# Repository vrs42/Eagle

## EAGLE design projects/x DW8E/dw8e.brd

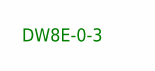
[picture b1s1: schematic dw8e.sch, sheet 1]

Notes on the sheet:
DW8E-0-3

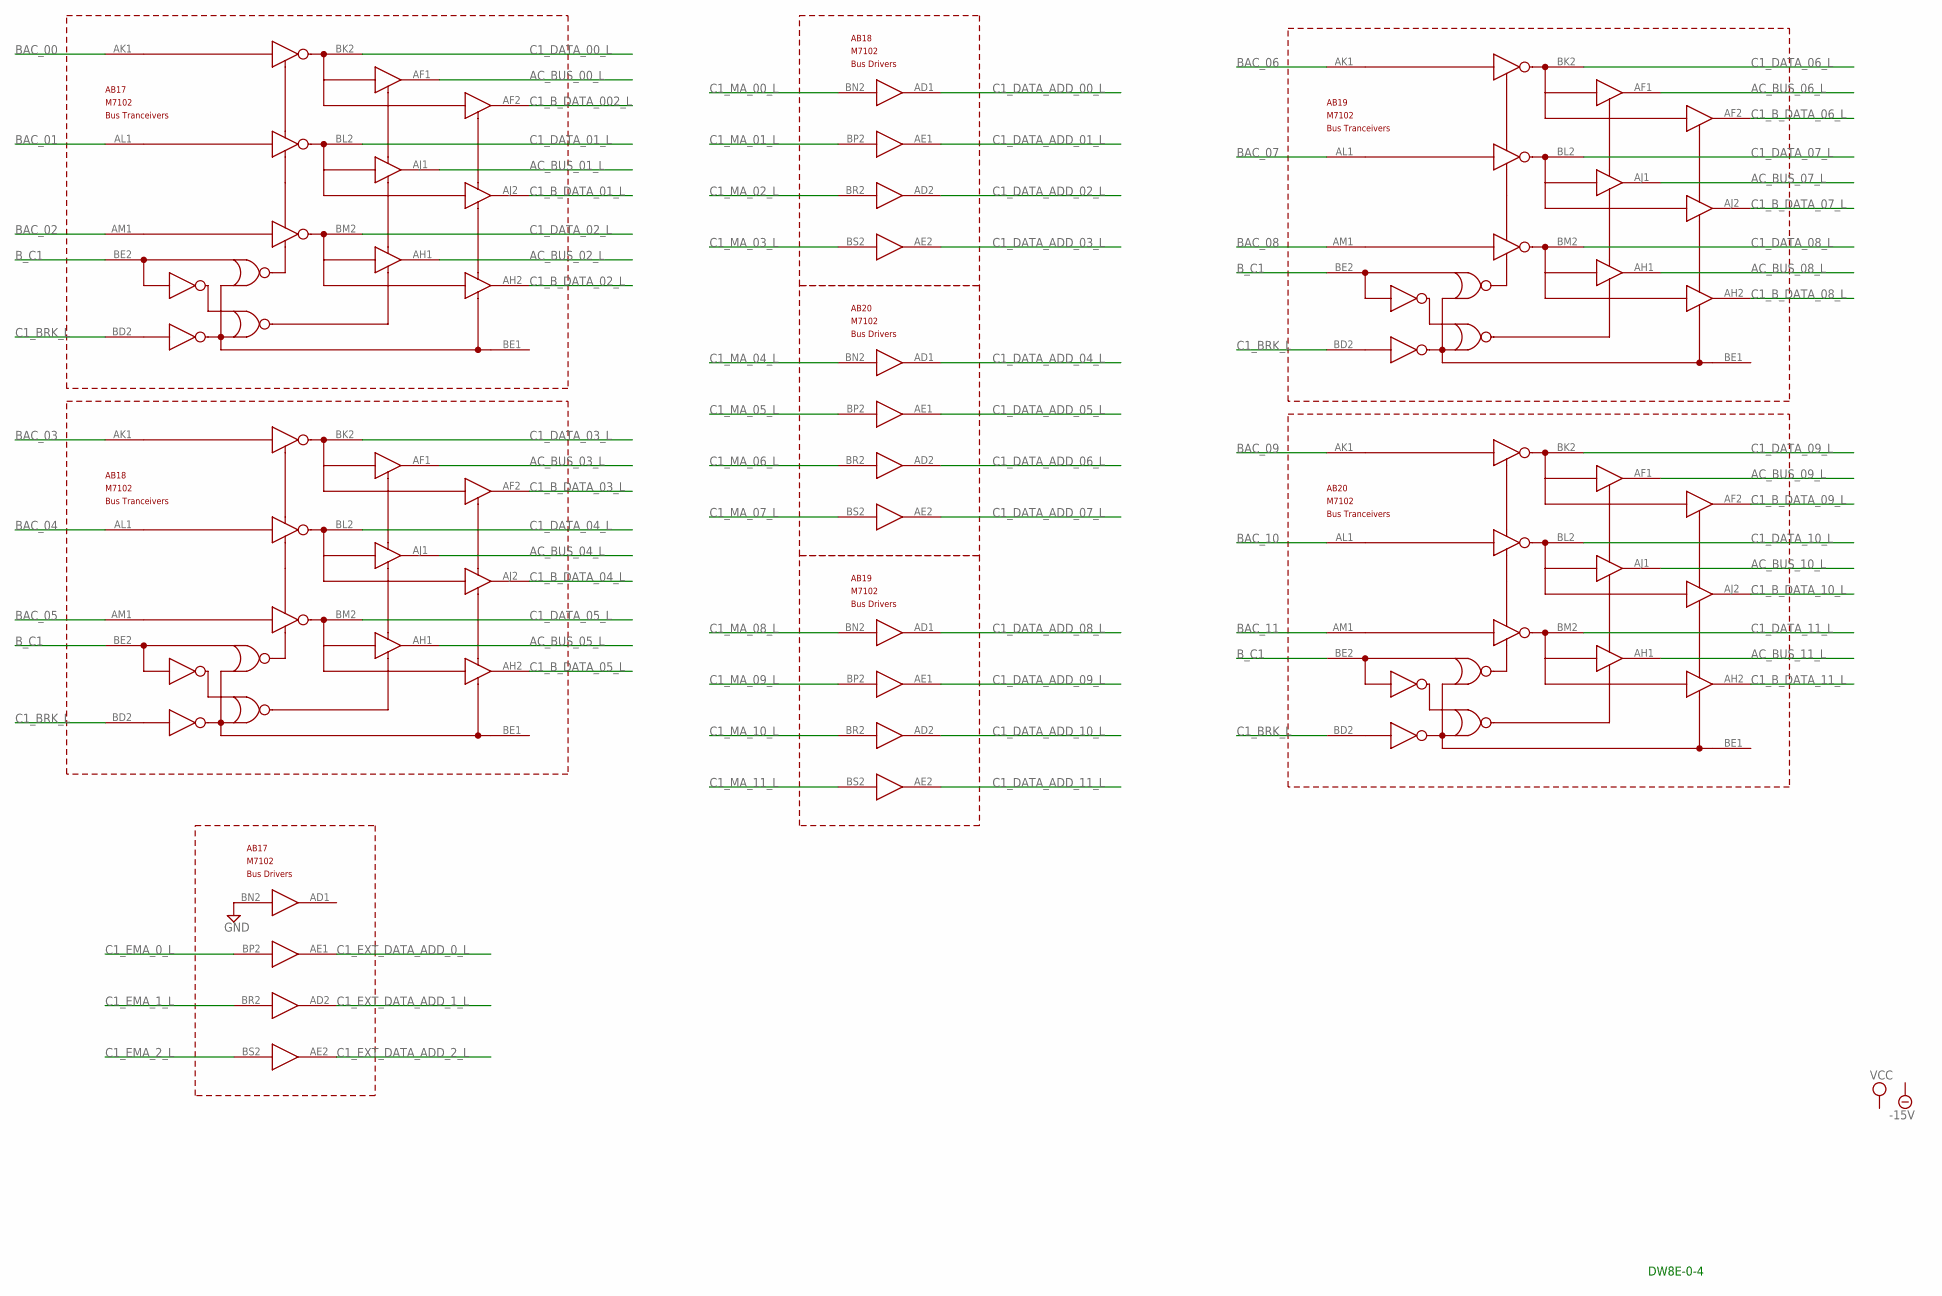
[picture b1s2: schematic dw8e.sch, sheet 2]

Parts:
AB17, AB18, AB19, AB20: M7102; H807-2

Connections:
-15V: AB17.AB2 (-15V), AB17.BB2 (-15V), AB18.AB2 (-15V), AB18.BB2 (-15V), AB19.AB2 (-15V), AB19.BB2 (-15V), AB20.AB2 (-15V), AB20.BB2 (-15V); also elsewhere on the board
AC_BUS_00_L: AB17.AF1
AC_BUS_01_L: AB17.AJ1
AC_BUS_02_L: AB17.AH1
AC_BUS_03_L: AB18.AF1
AC_BUS_04_L: AB18.AJ1
AC_BUS_05_L: AB18.AH1
AC_BUS_06_L: AB19.AF1
AC_BUS_07_L: AB19.AJ1
AC_BUS_08_L: AB19.AH1
AC_BUS_09_L: AB20.AF1
AC_BUS_10_L: AB20.AJ1
AC_BUS_11_L: AB20.AH1
BAC_00: AB17.AK1; also elsewhere on the board
BAC_01: AB17.AL1; also elsewhere on the board
BAC_02: AB17.AM1; also elsewhere on the board
BAC_03: AB18.AK1; also elsewhere on the board
BAC_04: AB18.AL1; also elsewhere on the board
BAC_05: AB18.AM1; also elsewhere on the board
BAC_06: AB19.AK1; also elsewhere on the board
BAC_07: AB19.AL1; also elsewhere on the board
BAC_08: AB19.AM1; also elsewhere on the board
BAC_09: AB20.AK1; also elsewhere on the board
BAC_10: AB20.AL1; also elsewhere on the board
BAC_11: AB20.AM1; also elsewhere on the board
B_C1: AB17.BE2, AB18.BE2, AB19.BE2, AB20.BE2
C1_BRK_L: AB17.BD2, AB18.BD2, AB19.BD2, AB20.BD2; also elsewhere on the board
C1_B_DATA_01_L: AB17.AJ2
C1_B_DATA_002_L: AB17.AF2
C1_B_DATA_02_L: AB17.AH2
C1_B_DATA_03_L: AB18.AF2
C1_B_DATA_04_L: AB18.AJ2
C1_B_DATA_05_L: AB18.AH2
C1_B_DATA_06_L: AB19.AF2
C1_B_DATA_07_L: AB19.AJ2
C1_B_DATA_08_L: AB19.AH2
C1_B_DATA_09_L: AB20.AF2
C1_B_DATA_10_L: AB20.AJ2
C1_B_DATA_11_L: AB20.AH2
C1_DATA_00_L: AB17.BK2
C1_DATA_01_L: AB17.BL2
C1_DATA_02_L: AB17.BM2
C1_DATA_03_L: AB18.BK2
C1_DATA_04_L: AB18.BL2
C1_DATA_05_L: AB18.BM2
C1_DATA_06_L: AB19.BK2
C1_DATA_07_L: AB19.BL2
C1_DATA_08_L: AB19.BM2
C1_DATA_09_L: AB20.BK2
C1_DATA_10_L: AB20.BL2
C1_DATA_11_L: AB20.BM2
C1_DATA_ADD_00_L: AB18.AD1; also elsewhere on the board
C1_DATA_ADD_01_L: AB18.AE1; also elsewhere on the board
C1_DATA_ADD_02_L: AB18.AD2; also elsewhere on the board
C1_DATA_ADD_03_L: AB18.AE2; also elsewhere on the board
C1_DATA_ADD_04_L: AB20.AD1; also elsewhere on the board
C1_DATA_ADD_05_L: AB20.AE1; also elsewhere on the board
C1_DATA_ADD_06_L: AB20.AD2; also elsewhere on the board
C1_DATA_ADD_07_L: AB20.AE2; also elsewhere on the board
C1_DATA_ADD_08_L: AB19.AD1; also elsewhere on the board
C1_DATA_ADD_09_L: AB19.AE1; also elsewhere on the board
C1_DATA_ADD_10_L: AB19.AD2; also elsewhere on the board
C1_DATA_ADD_11_L: AB19.AE2; also elsewhere on the board
C1_EMA_0_L: AB17.BP2
C1_EMA_1_L: AB17.BR2
C1_EMA_2_L: AB17.BS2
C1_EXT_DATA_ADD_0_L: AB17.AE1; also elsewhere on the board
C1_EXT_DATA_ADD_1_L: AB17.AD2; also elsewhere on the board
C1_EXT_DATA_ADD_2_L: AB17.AE2; also elsewhere on the board
C1_MA_00_L: AB18.BN2
C1_MA_01_L: AB18.BP2
C1_MA_02_L: AB18.BR2
C1_MA_03_L: AB18.BS2
C1_MA_04_L: AB20.BN2
C1_MA_05_L: AB20.BP2
C1_MA_06_L: AB20.BR2
C1_MA_07_L: AB20.BS2
C1_MA_08_L: AB19.BN2
C1_MA_09_L: AB19.BP2
C1_MA_10_L: AB19.BR2
C1_MA_11_L: AB19.BS2
GND: AB17.AC2 (GND), AB17.AT1 (GND), AB17.BC2 (GND), AB17.BN2, AB17.BT1 (GND), AB18.AC2 (GND), AB18.AT1 (GND), AB18.BC2 (GND), AB18.BT1 (GND), AB19.AC2 (GND), AB19.AT1 (GND), AB19.BC2 (GND), AB19.BT1 (GND), AB20.AC2 (GND), AB20.AT1 (GND), AB20.BC2 (GND), AB20.BT1 (GND); also elsewhere on the board
VCC: AB17.AA2 (VCC), AB17.BA2 (VCC), AB18.AA2 (VCC), AB18.BA2 (VCC), AB19.AA2 (VCC), AB19.BA2 (VCC), AB20.AA2 (VCC), AB20.BA2 (VCC); also elsewhere on the board

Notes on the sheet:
DW8E-0-4

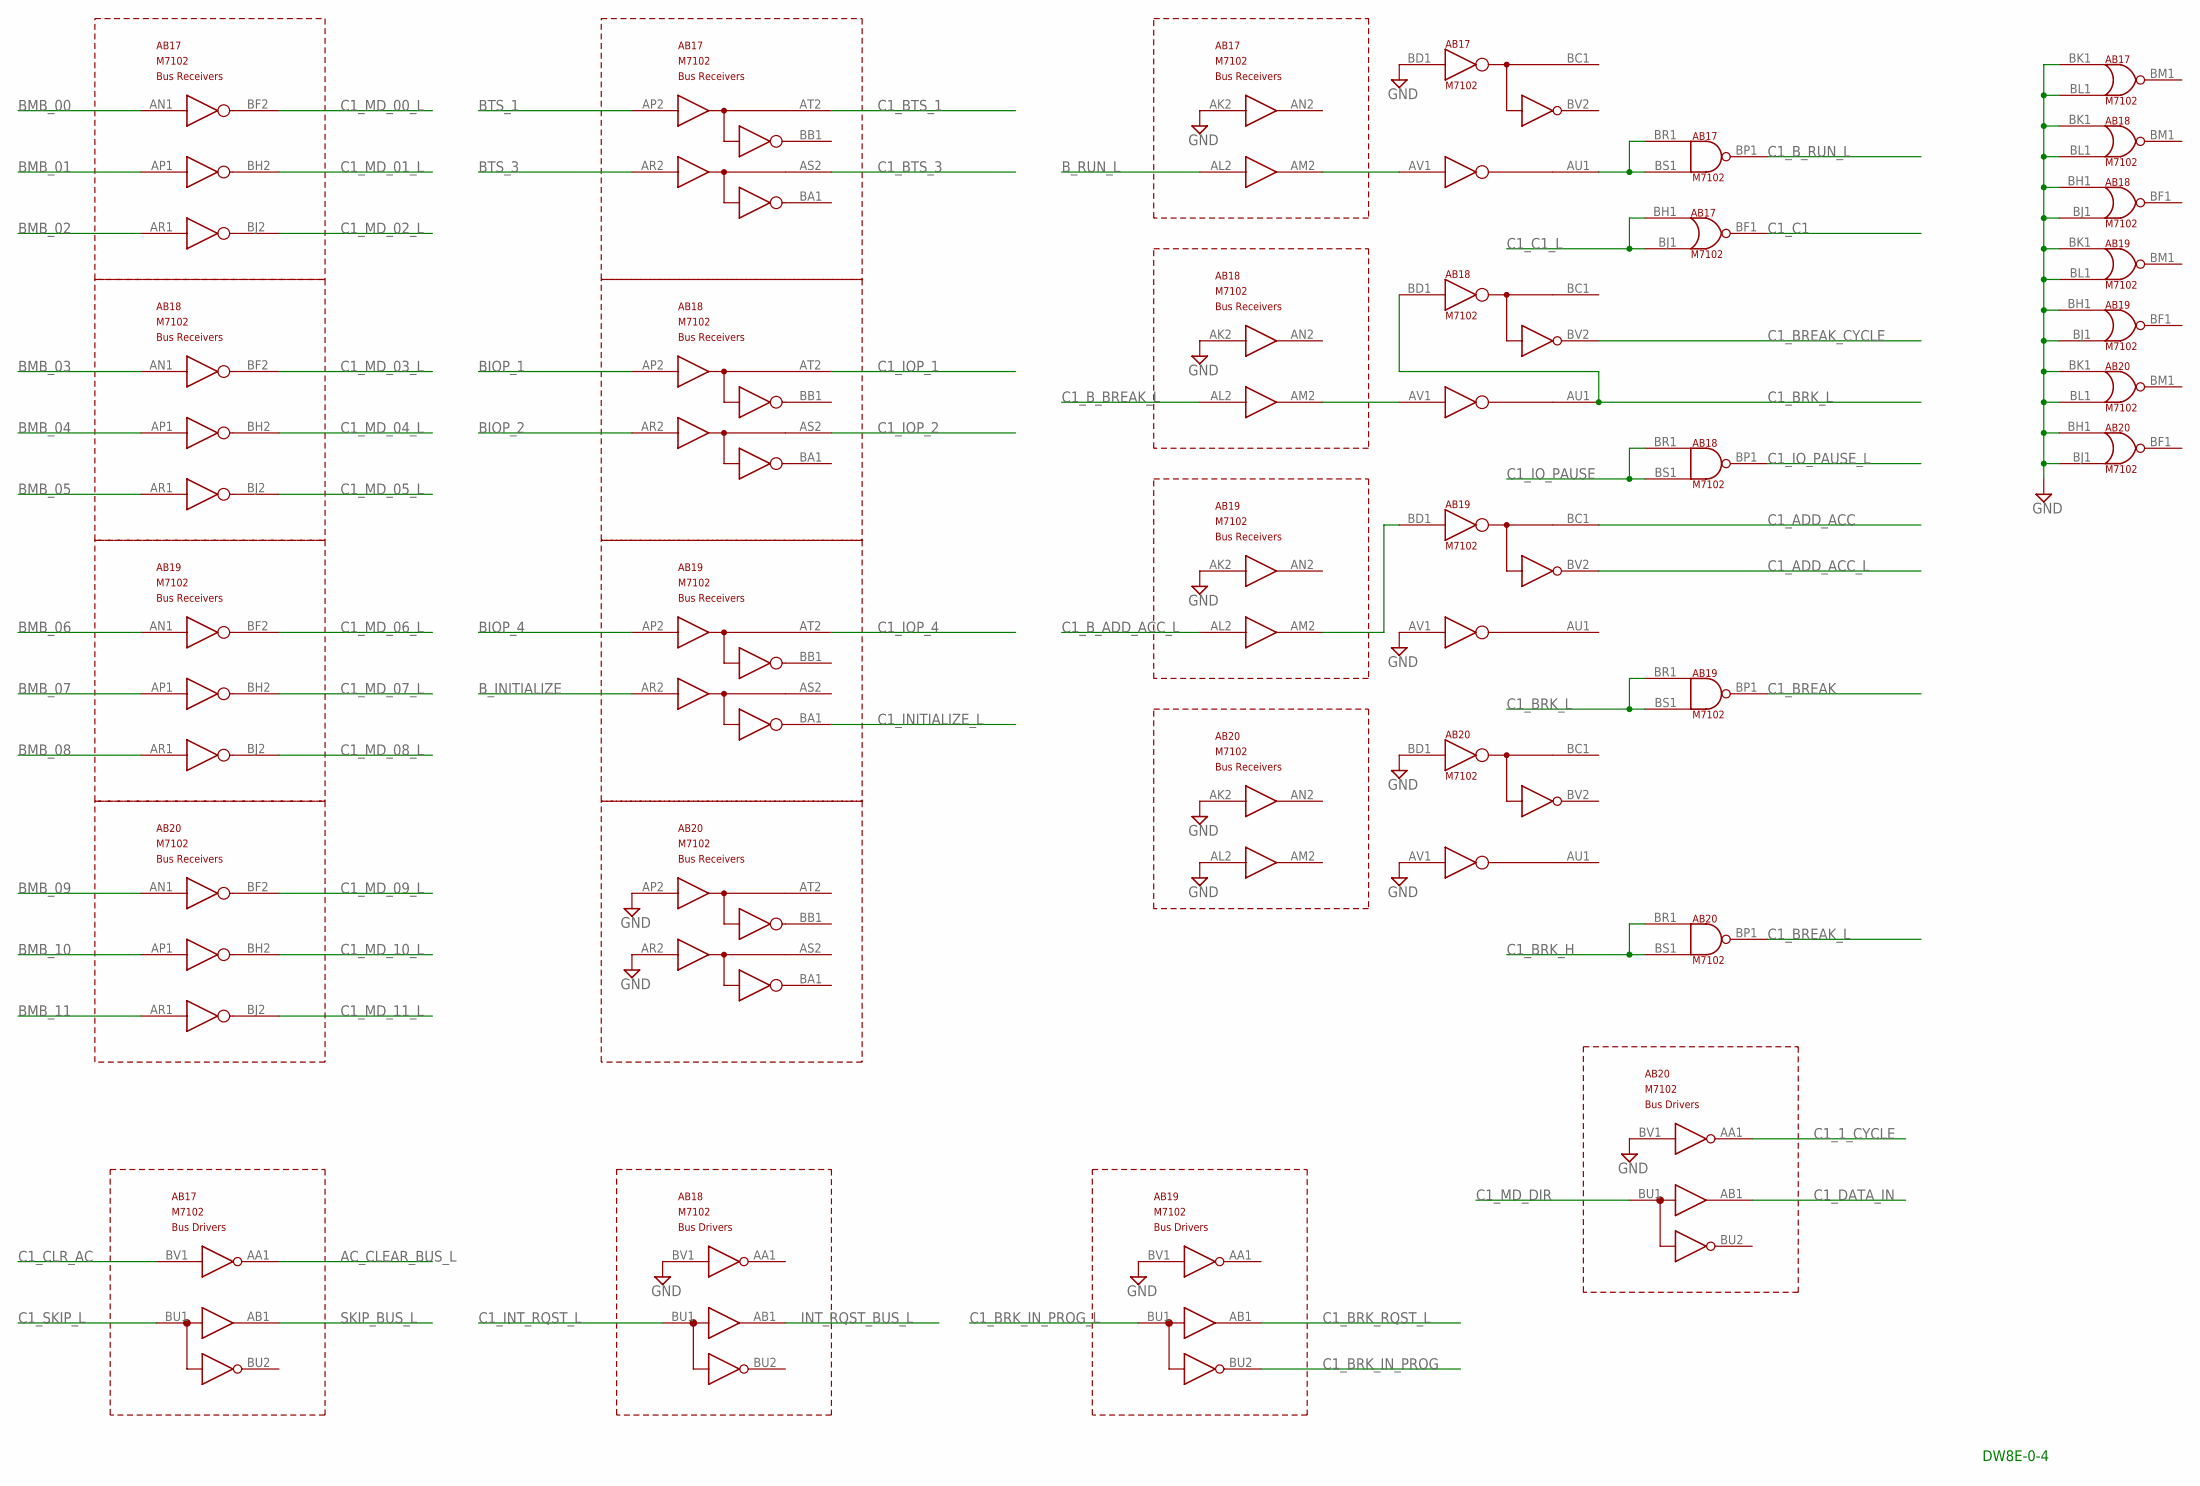
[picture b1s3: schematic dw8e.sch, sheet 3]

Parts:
AB17, AB18, AB19, AB20: M7102; H807-2

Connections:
-15V: AB17.AB2 (-15V), AB17.BB2 (-15V), AB18.AB2 (-15V), AB18.BB2 (-15V), AB19.AB2 (-15V), AB19.BB2 (-15V), AB20.AB2 (-15V), AB20.BB2 (-15V); also elsewhere on the board
AC_CLEAR_BUS_L: AB17.AA1; also elsewhere on the board
BIOP_1: AB18.AP2
BIOP_2: AB18.AR2
BIOP_4: AB19.AP2
BMB_00: AB17.AN1; also elsewhere on the board
BMB_01: AB17.AP1; also elsewhere on the board
BMB_02: AB17.AR1; also elsewhere on the board
BMB_03: AB18.AN1; also elsewhere on the board
BMB_04: AB18.AP1; also elsewhere on the board
BMB_05: AB18.AR1; also elsewhere on the board
BMB_06: AB19.AN1; also elsewhere on the board
BMB_07: AB19.AP1; also elsewhere on the board
BMB_08: AB19.AR1; also elsewhere on the board
BMB_09: AB20.AN1; also elsewhere on the board
BMB_10: AB20.AP1; also elsewhere on the board
BMB_11: AB20.AR1; also elsewhere on the board
BTS_1: AB17.AP2; also elsewhere on the board
BTS_3: AB17.AR2; also elsewhere on the board
B_INITIALIZE: AB19.AR2; also elsewhere on the board
B_RUN_L: AB17.AL2; also elsewhere on the board
C1_1_CYCLE: AB20.AA1; also elsewhere on the board
C1_ADD_ACC: AB19.BC1
C1_ADD_ACC_L: AB19.BV2
C1_BREAK: AB19.BP1 (OUT)
C1_BREAK_CYCLE: AB18.BV2
C1_BREAK_L: AB20.BP1 (OUT)
C1_BRK_H: AB20.BR1 (IN1), AB20.BS1 (IN2)
C1_BRK_IN_PROG: AB19.BU2
C1_BRK_IN_PROG_L: AB19.BU1
C1_BRK_L: AB18.AU1, AB18.BD1, AB19.BR1 (IN1), AB19.BS1 (IN2); also elsewhere on the board
C1_BRK_RQST_L: AB19.AB1; also elsewhere on the board
C1_BTS_1: AB17.AT2
C1_BTS_3: AB17.AS2
C1_B_ADD_ACC_L: AB19.AL2
C1_B_BREAK_L: AB18.AL2; also elsewhere on the board
C1_B_RUN_L: AB17.BP1 (OUT)
C1_C1: AB17.BF1 (OUT)
C1_C1_L: AB17.BH1 (IN1), AB17.BJ1 (IN2)
C1_CLR_AC: AB17.BV1
C1_DATA_IN: AB20.AB1; also elsewhere on the board
C1_INITIALIZE_L: AB19.BA1
C1_INT_RQST_L: AB18.BU1
C1_IOP_1: AB18.AT2
C1_IOP_2: AB18.AS2
C1_IOP_4: AB19.AT2
C1_IO_PAUSE: AB18.BR1 (IN1), AB18.BS1 (IN2)
C1_IO_PAUSE_L: AB18.BP1 (OUT)
C1_MD_00_L: AB17.BF2
C1_MD_01_L: AB17.BH2
C1_MD_02_L: AB17.BJ2
C1_MD_03_L: AB18.BF2
C1_MD_04_L: AB18.BH2
C1_MD_05_L: AB18.BJ2
C1_MD_06_L: AB19.BF2
C1_MD_07_L: AB19.BH2
C1_MD_08_L: AB19.BJ2
C1_MD_09_L: AB20.BF2
C1_MD_10_L: AB20.BH2
C1_MD_11_L: AB20.BJ2
C1_MD_DIR: AB20.BU1
C1_SKIP_L: AB17.BU1
GND: AB17.AC2 (GND), AB17.AK2, AB17.AT1 (GND), AB17.BC2 (GND), AB17.BD1, AB17.BK1 (IN1), AB17.BL1 (IN2), AB17.BT1 (GND), AB18.AC2 (GND), AB18.AK2, AB18.AT1 (GND), AB18.BC2 (GND), AB18.BH1 (IN1), AB18.BJ1 (IN2), AB18.BK1 (IN1), AB18.BL1 (IN2), AB18.BT1 (GND), AB18.BV1, AB19.AC2 (GND), AB19.AK2, AB19.AT1 (GND), AB19.AV1, AB19.BC2 (GND), AB19.BH1 (IN1), AB19.BJ1 (IN2), AB19.BK1 (IN1), AB19.BL1 (IN2), AB19.BT1 (GND), AB19.BV1, AB20.AC2 (GND), AB20.AK2, AB20.AL2, AB20.AP2, AB20.AR2, AB20.AT1 (GND), AB20.AV1, AB20.BC2 (GND), AB20.BD1, AB20.BH1 (IN1), AB20.BJ1 (IN2), AB20.BK1 (IN1), AB20.BL1 (IN2), AB20.BT1 (GND), AB20.BV1; also elsewhere on the board
INT_RQST_BUS_L: AB18.AB1; also elsewhere on the board
unnamed: AB17.AU1, AB17.BR1 (IN1), AB17.BS1 (IN2)
unnamed: AB19.AM2, AB19.BD1
unnamed: AB18.AM2, AB18.AV1
unnamed: AB17.AM2, AB17.AV1
SKIP_BUS_L: AB17.AB1; also elsewhere on the board
VCC: AB17.AA2 (VCC), AB17.BA2 (VCC), AB18.AA2 (VCC), AB18.BA2 (VCC), AB19.AA2 (VCC), AB19.BA2 (VCC), AB20.AA2 (VCC), AB20.BA2 (VCC); also elsewhere on the board

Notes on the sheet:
DW8E-0-4

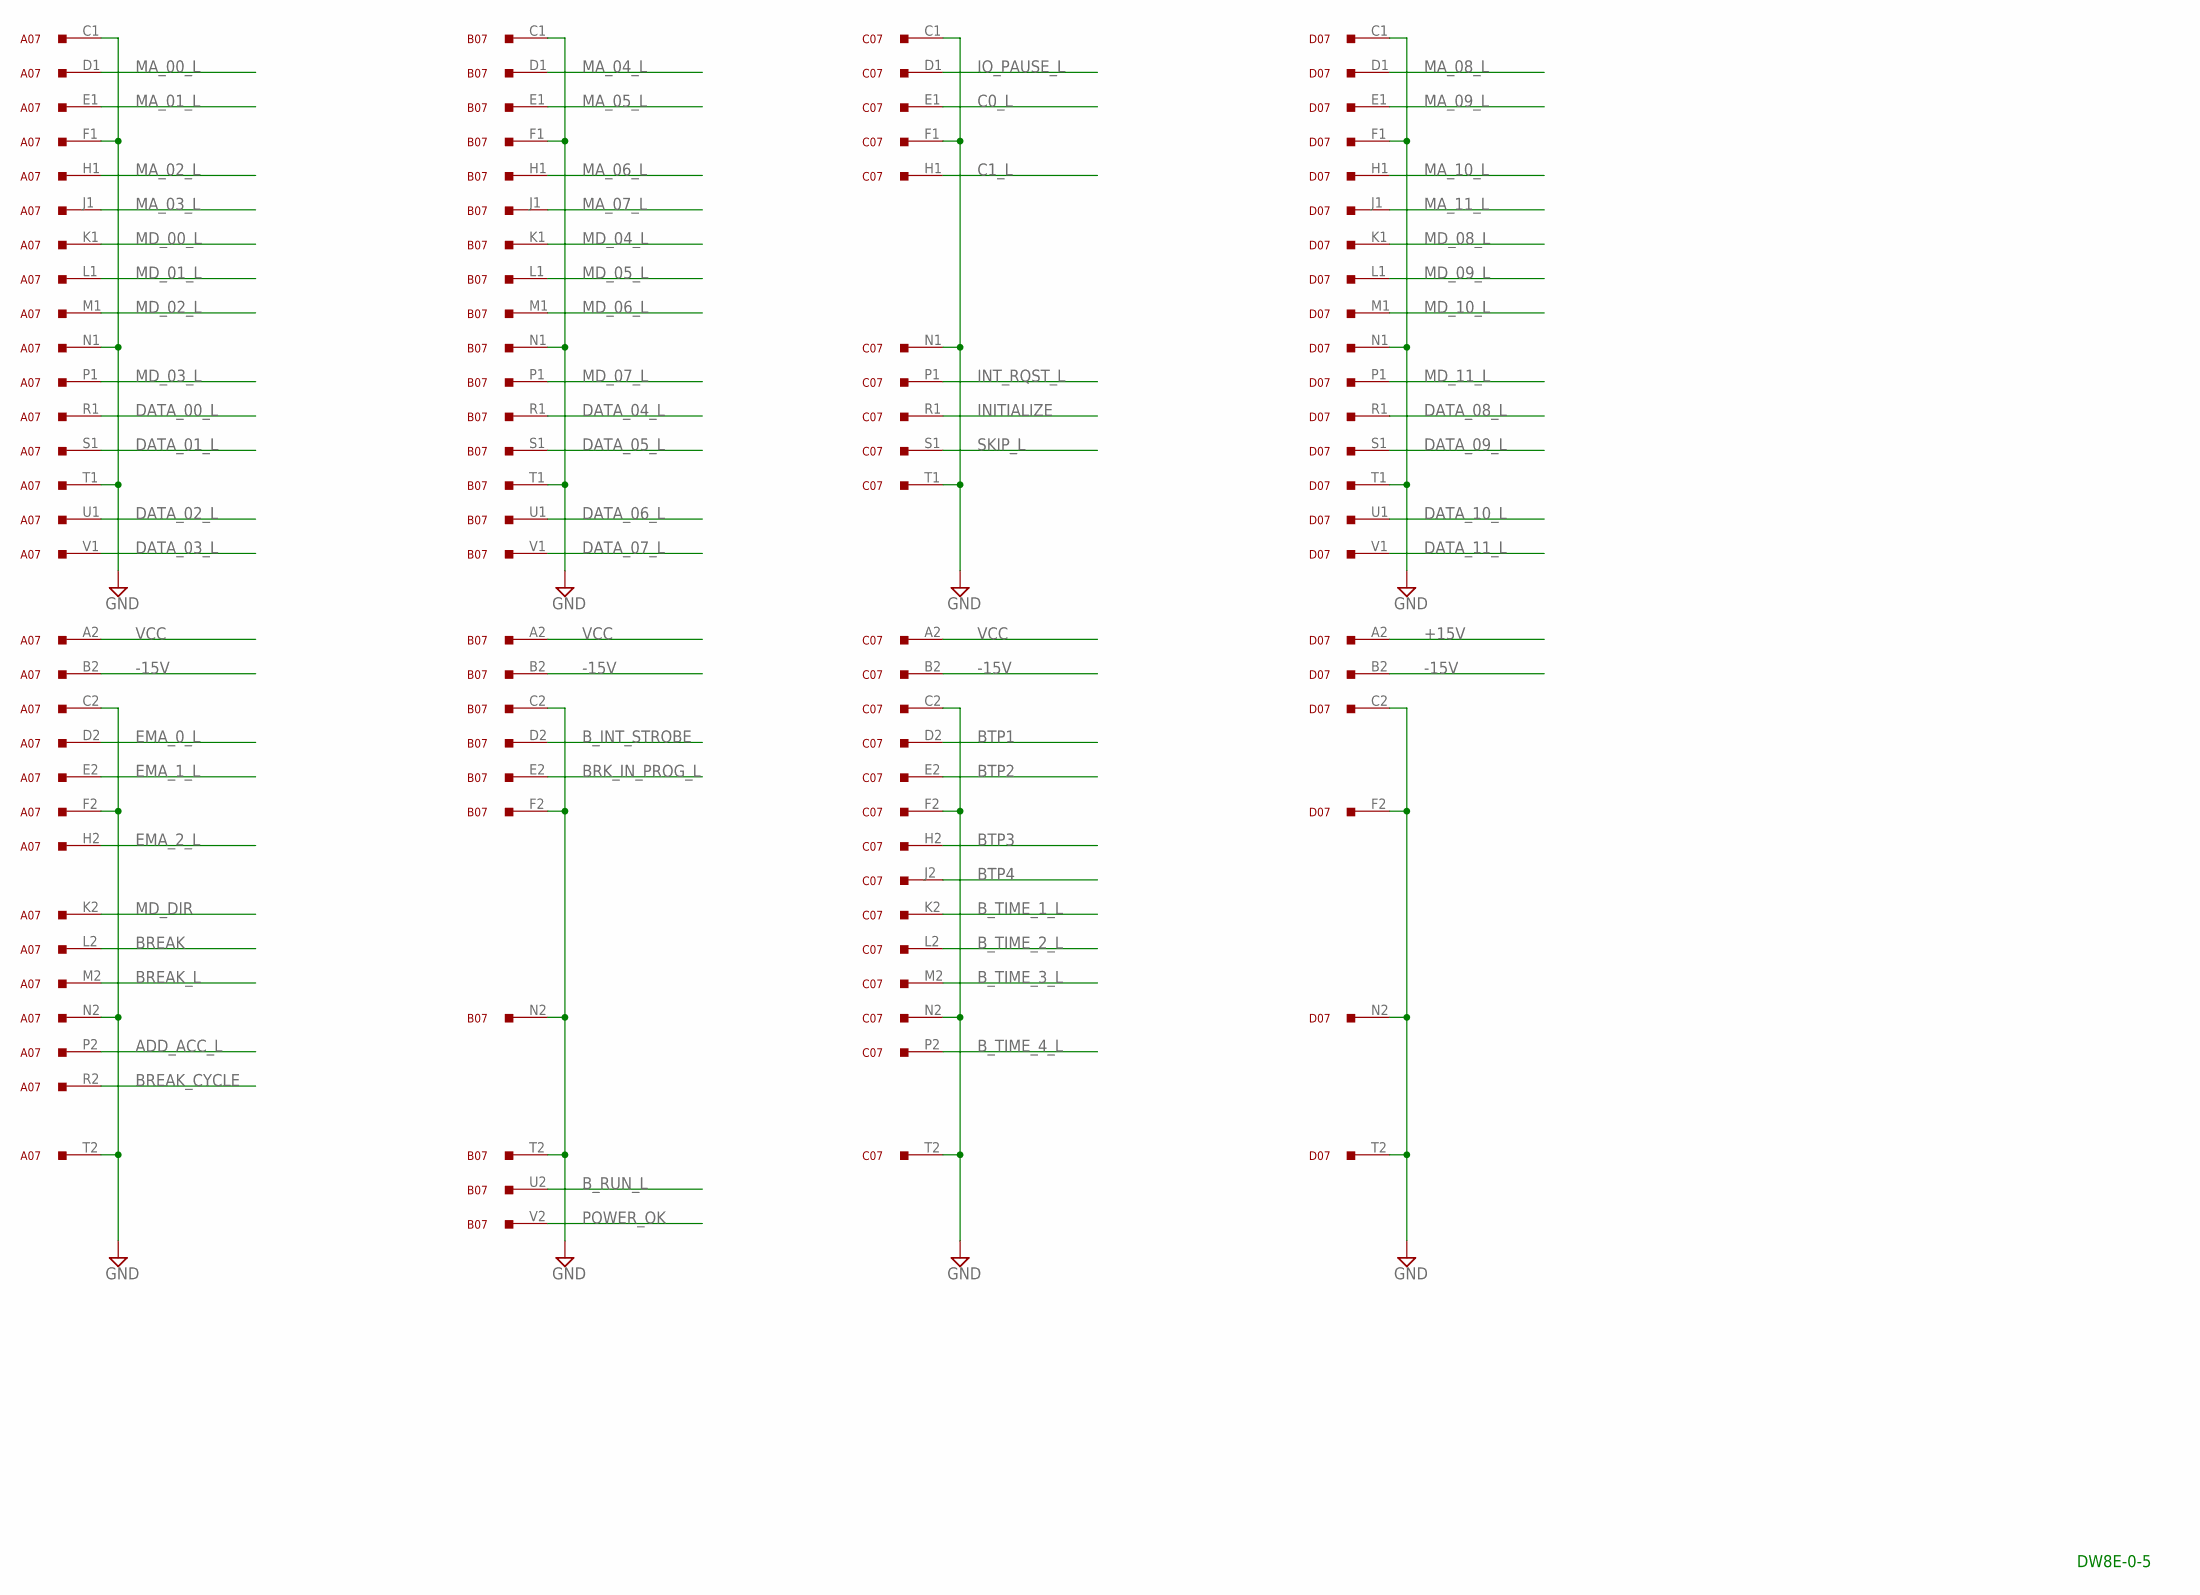
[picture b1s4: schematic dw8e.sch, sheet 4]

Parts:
A07: M916; H807
B07: M916; H807
C07: M916; H807
D07: M916; H807

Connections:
+15V: D07.A2
-15V: A07.B2, B07.B2, C07.B2, D07.B2; also elsewhere on the board
ADD_ACC_L: A07.P2
BREAK: A07.L2
BREAK_CYCLE: A07.R2
BREAK_L: A07.M2
BRK_IN_PROG_L: B07.E2
BTP1: C07.D2
BTP2: C07.E2
BTP3: C07.H2
BTP4: C07.J2
B_INT_STROBE: B07.D2
B_RUN_L: B07.U2; also elsewhere on the board
B_TIME_1_L: C07.K2
B_TIME_2_L: C07.L2
B_TIME_3_L: C07.M2
B_TIME_4_L: C07.P2
C0_L: C07.E1
C1_L: C07.H1
DATA_00_L: A07.R1
DATA_01_L: A07.S1
DATA_02_L: A07.U1
DATA_03_L: A07.V1
DATA_04_L: B07.R1
DATA_05_L: B07.S1
DATA_06_L: B07.U1
DATA_07_L: B07.V1
DATA_08_L: D07.R1
DATA_09_L: D07.S1
DATA_10_L: D07.U1
DATA_11_L: D07.V1
EMA_0_L: A07.D2
EMA_1_L: A07.E2
EMA_2_L: A07.H2
GND: A07.C1, A07.C2, A07.F1, A07.F2, A07.N1, A07.N2, A07.T1, A07.T2, B07.C1, B07.C2, B07.F1, B07.F2, B07.N1, B07.N2, B07.T1, B07.T2, C07.C1, C07.C2, C07.F1, C07.F2, C07.N1, C07.N2, C07.T1, C07.T2, D07.C1, D07.C2, D07.F1, D07.F2, D07.N1, D07.N2, D07.T1, D07.T2; also elsewhere on the board
INITIALIZE: C07.R1
INT_RQST_L: C07.P1
IO_PAUSE_L: C07.D1
MA_00_L: A07.D1
MA_01_L: A07.E1
MA_02_L: A07.H1
MA_03_L: A07.J1
MA_04_L: B07.D1
MA_05_L: B07.E1
MA_06_L: B07.H1
MA_07_L: B07.J1
MA_08_L: D07.D1
MA_09_L: D07.E1
MA_10_L: D07.H1
MA_11_L: D07.J1
MD_00_L: A07.K1
MD_01_L: A07.L1
MD_02_L: A07.M1
MD_03_L: A07.P1
MD_04_L: B07.K1
MD_05_L: B07.L1
MD_06_L: B07.M1
MD_07_L: B07.P1
MD_08_L: D07.K1
MD_09_L: D07.L1
MD_10_L: D07.M1
MD_11_L: D07.P1
MD_DIR: A07.K2
POWER_OK: B07.V2
SKIP_L: C07.S1
VCC: A07.A2, B07.A2, C07.A2; also elsewhere on the board

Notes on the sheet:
DW8E-0-5

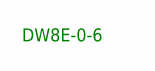
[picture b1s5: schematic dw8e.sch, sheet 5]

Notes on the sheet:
DW8E-0-6

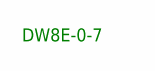
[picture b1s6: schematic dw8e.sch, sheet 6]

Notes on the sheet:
DW8E-0-7

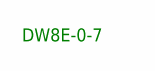
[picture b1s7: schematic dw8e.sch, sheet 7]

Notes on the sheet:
DW8E-0-7

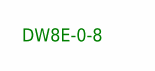
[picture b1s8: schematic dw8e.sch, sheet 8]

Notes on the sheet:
DW8E-0-8

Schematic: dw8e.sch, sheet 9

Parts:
C18, C19, C20: M903; H807
D18, D19, D20: M903; H807

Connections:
AC_00_BUS_L: C18.B1, D18.B1
AC_01_BUS_L: C18.D1, D18.D1
AC_02_BUS_L: C18.E1, D18.E1
AC_03_BUS_L: C18.H1, D18.H1
AC_04_BUS_L: C18.J1, D18.J1
AC_05_BUS_L: C18.L1, D18.L1
AC_06_BUS_L: C18.M1, D18.M1
AC_07_BUS_L: C18.P1, D18.P1
AC_08_BUS_L: C18.S1, D18.S1
AC_09_BUS_L: C18.D2, D18.D2
AC_10_BUS_L: C18.E2, D18.E2
AC_11_BUS_L: C18.H2, D18.H2
AC_CLEAR_BUS_L: C18.P2, D18.P2; also elsewhere on the board
BAC_00: C20.B1, D20.B1; also elsewhere on the board
BAC_01: C20.D1, D20.D1; also elsewhere on the board
BAC_02: C20.E1, D20.E1; also elsewhere on the board
BAC_03: C20.H1, D20.H1; also elsewhere on the board
BAC_04: C20.J1, D20.J1; also elsewhere on the board
BAC_05: C20.L1, D20.L1; also elsewhere on the board
BAC_06: C20.M1, D20.M1; also elsewhere on the board
BAC_07: C20.P1, D20.P1; also elsewhere on the board
BAC_08: C20.S1, D20.S1; also elsewhere on the board
BAC_09: C20.D2, D20.D2; also elsewhere on the board
BAC_10: C20.E2, D20.E2; also elsewhere on the board
BAC_11: C20.H2, D20.H2; also elsewhere on the board
BIOP1: C20.K2, D20.K2
BIOP2: C20.M2, D20.M2
BIOP4: C20.P2, D20.P2
BMB_00: C19.B1, D19.B1; also elsewhere on the board
BMB_01: C19.D1, D19.D1; also elsewhere on the board
BMB_02: C19.E1, D19.E1; also elsewhere on the board
BMB_03: C19.J1, D19.J1; also elsewhere on the board
BMB_03_L: C19.H1, D19.H1
BMB_04: C19.M1, D19.M1; also elsewhere on the board
BMB_05: C19.S1, D19.S1; also elsewhere on the board
BMB_05_L: C19.P1, D19.P1
BMB_06: C19.E2, D19.E2; also elsewhere on the board
BMB_06_L: C19.D2, D19.D2
BMB_07: C19.K2, D19.K2; also elsewhere on the board
BMB_07_L: C19.H2, D19.H2
BMB_08: C19.P2, D19.P2; also elsewhere on the board
BMB_08_L: C19.M2, D19.M2
BMB_09: C19.S2, D19.S2; also elsewhere on the board
BMB_10: C19.T2, D19.T2; also elsewhere on the board
BMB_11: C19.V2, D19.V2; also elsewhere on the board
BTS_1: C20.T2, D20.T2; also elsewhere on the board
BTS_3: C20.S2, D20.S2; also elsewhere on the board
B_INITIALIZE: C20.V2, D20.V2; also elsewhere on the board
B_RUN_L: C18.S2, D18.S2; also elsewhere on the board
B_TT_INST: C18.T2, D18.T2
GND: C18.A1 (GND), C18.C1 (GND), C18.C2 (GND), C18.F1 (GND), C18.F2 (GND), C18.J2 (GND), C18.K1 (GND), C18.L2 (GND), C18.N1 (GND), C18.N2 (GND), C18.R1 (GND), C18.R2 (GND), C18.T1 (GND), C18.U2 (GND), C19.A1 (GND), C19.C1 (GND), C19.C2 (GND), C19.F1 (GND), C19.F2 (GND), C19.J2 (GND), C19.K1 (GND), C19.L2 (GND), C19.N1 (GND), C19.N2 (GND), C19.R1 (GND), C19.R2 (GND), C19.T1 (GND), C19.U2 (GND), C20.A1 (GND), C20.C1 (GND), C20.C2 (GND), C20.F1 (GND), C20.F2 (GND), C20.J2 (GND), C20.K1 (GND), C20.L2 (GND), C20.N1 (GND), C20.N2 (GND), C20.R1 (GND), C20.R2 (GND), C20.T1 (GND), C20.U2 (GND), D18.A1 (GND), D18.C1 (GND), D18.C2 (GND), D18.F1 (GND), D18.F2 (GND), D18.J2 (GND), D18.K1 (GND), D18.L2 (GND), D18.N1 (GND), D18.N2 (GND), D18.R1 (GND), D18.R2 (GND), D18.T1 (GND), D18.U2 (GND), D19.A1 (GND), D19.C1 (GND), D19.C2 (GND), D19.F1 (GND), D19.F2 (GND), D19.J2 (GND), D19.K1 (GND), D19.L2 (GND), D19.N1 (GND), D19.N2 (GND), D19.R1 (GND), D19.R2 (GND), D19.T1 (GND), D19.U2 (GND), D20.A1 (GND), D20.C1 (GND), D20.C2 (GND), D20.F1 (GND), D20.F2 (GND), D20.J2 (GND), D20.K1 (GND), D20.L2 (GND), D20.N1 (GND), D20.N2 (GND), D20.R1 (GND), D20.R2 (GND), D20.T1 (GND), D20.U2 (GND); also elsewhere on the board
INT_RQST_BUS_L: C18.M2, D18.M2; also elsewhere on the board
LINE_MUX_L: C18.V2, D18.V2
MBM_04_L: C19.L1, D19.L1
SKIP_BUS_L: C18.K2, D18.K2; also elsewhere on the board

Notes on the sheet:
DW8E-0-2
* Used only in 8/i

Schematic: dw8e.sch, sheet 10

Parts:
C16, C17: M903; H807
D16, D17: M903; H807

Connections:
C1_1_CYCLE: C16.K2, D16.K2; also elsewhere on the board
C1_BADD_ACC_0_L: C17.S2, D17.S2
C1_BRK_RQST_L: C17.K2, D17.K2; also elsewhere on the board
C1_B_BREAK_L: C17.P2, D17.P2; also elsewhere on the board
C1_B_DATA_00: C16.B1, D16.B1
C1_B_DATA_01: C16.D1, D16.D1
C1_B_DATA_02: C16.E1, D16.E1
C1_B_DATA_03: C16.H1, D16.H1
C1_B_DATA_04: C16.J1, D16.J1
C1_B_DATA_05: C16.L1, D16.L1
C1_B_DATA_06: C16.M1, D16.M1
C1_B_DATA_07: C16.P1, D16.P1
C1_B_DATA_08: C16.S1, D16.S1
C1_B_DATA_09: C16.D2, D16.D2
C1_B_DATA_10: C16.E2, D16.E2
C1_B_DATA_11: C16.H2, D16.H2
C1_B_INITIALIZE_2: C17.V2, D17.V2
C1_B_WC_OVERFLOW_L: C16.P2, D16.P2
C1_CA_INCREMENT_L: C16.M2, D16.M2
C1_DATA_ADD_00_L: C17.B1, D17.B1; also elsewhere on the board
C1_DATA_ADD_01_L: C17.D1, D17.D1; also elsewhere on the board
C1_DATA_ADD_02_L: C17.E1, D17.E1; also elsewhere on the board
C1_DATA_ADD_03_L: C17.H1, D17.H1; also elsewhere on the board
C1_DATA_ADD_04_L: C17.J1, D17.J1; also elsewhere on the board
C1_DATA_ADD_05_L: C17.L1, D17.L1; also elsewhere on the board
C1_DATA_ADD_06_L: C17.M1, D17.M1; also elsewhere on the board
C1_DATA_ADD_07_L: C17.P1, D17.P1; also elsewhere on the board
C1_DATA_ADD_08_L: C17.S1, D17.S1; also elsewhere on the board
C1_DATA_ADD_09_L: C17.D2, D17.D2; also elsewhere on the board
C1_DATA_ADD_10_L: C17.E2, D17.E2; also elsewhere on the board
C1_DATA_ADD_11_L: C17.H2, D17.H2; also elsewhere on the board
C1_DATA_IN: C17.M2, D17.M2; also elsewhere on the board
C1_EXT_DATA_ADD_0_L: C16.V2, D16.V2; also elsewhere on the board
C1_EXT_DATA_ADD_1_L: C16.T2, D16.T2; also elsewhere on the board
C1_EXT_DATA_ADD_2_L: C16.S2, D16.S2; also elsewhere on the board
C1_MB_INCREMENT_L: C17.T2, D17.T2
GND: C16.A1 (GND), C16.C1 (GND), C16.C2 (GND), C16.F1 (GND), C16.F2 (GND), C16.J2 (GND), C16.K1 (GND), C16.L2 (GND), C16.N1 (GND), C16.N2 (GND), C16.R1 (GND), C16.R2 (GND), C16.T1 (GND), C16.U2 (GND), C17.A1 (GND), C17.C1 (GND), C17.C2 (GND), C17.F1 (GND), C17.F2 (GND), C17.J2 (GND), C17.K1 (GND), C17.L2 (GND), C17.N1 (GND), C17.N2 (GND), C17.R1 (GND), C17.R2 (GND), C17.T1 (GND), C17.U2 (GND), D16.A1 (GND), D16.C1 (GND), D16.C2 (GND), D16.F1 (GND), D16.F2 (GND), D16.J2 (GND), D16.K1 (GND), D16.L2 (GND), D16.N1 (GND), D16.N2 (GND), D16.R1 (GND), D16.R2 (GND), D16.T1 (GND), D16.U2 (GND), D17.A1 (GND), D17.C1 (GND), D17.C2 (GND), D17.F1 (GND), D17.F2 (GND), D17.J2 (GND), D17.K1 (GND), D17.L2 (GND), D17.N1 (GND), D17.N2 (GND), D17.R1 (GND), D17.R2 (GND), D17.T1 (GND), D17.U2 (GND); also elsewhere on the board

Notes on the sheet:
DW8E-0-2

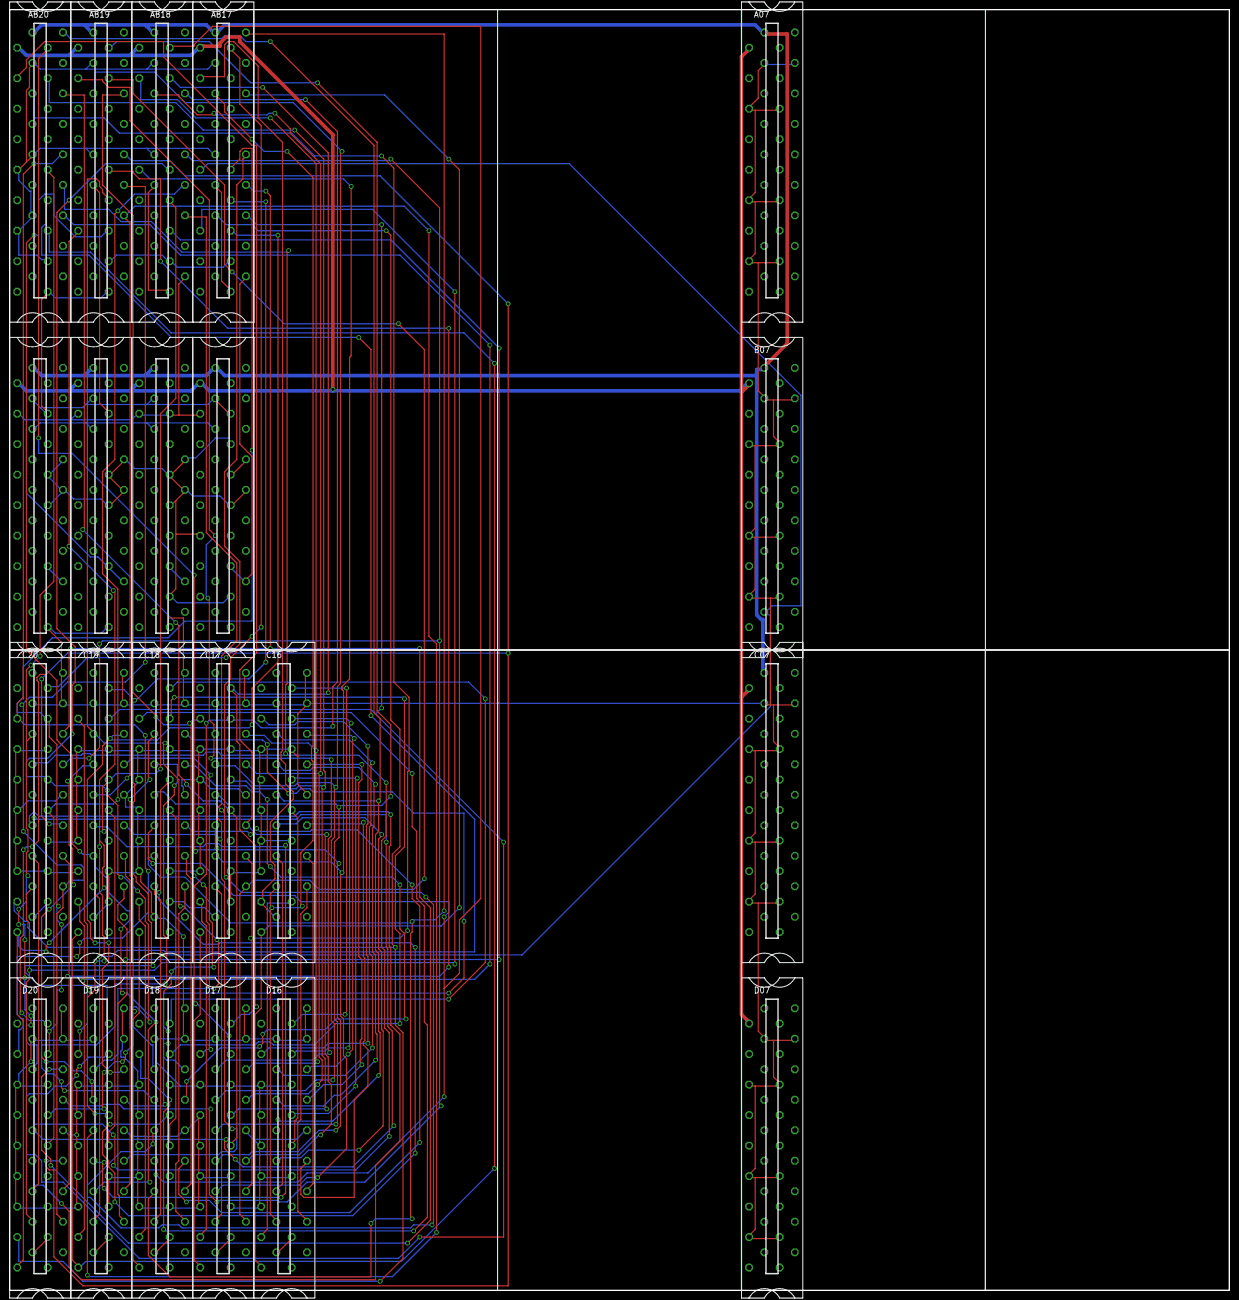
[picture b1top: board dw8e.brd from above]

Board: 2 copper layers, 254.0 x 266.7 mm, 29 parts (0 on the bottom side), 102 nets.

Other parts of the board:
U$1, U$2, U$3, U$4, U$6, U$7, U$8, U$9, U$10, U$11, U$12: CBLOCK

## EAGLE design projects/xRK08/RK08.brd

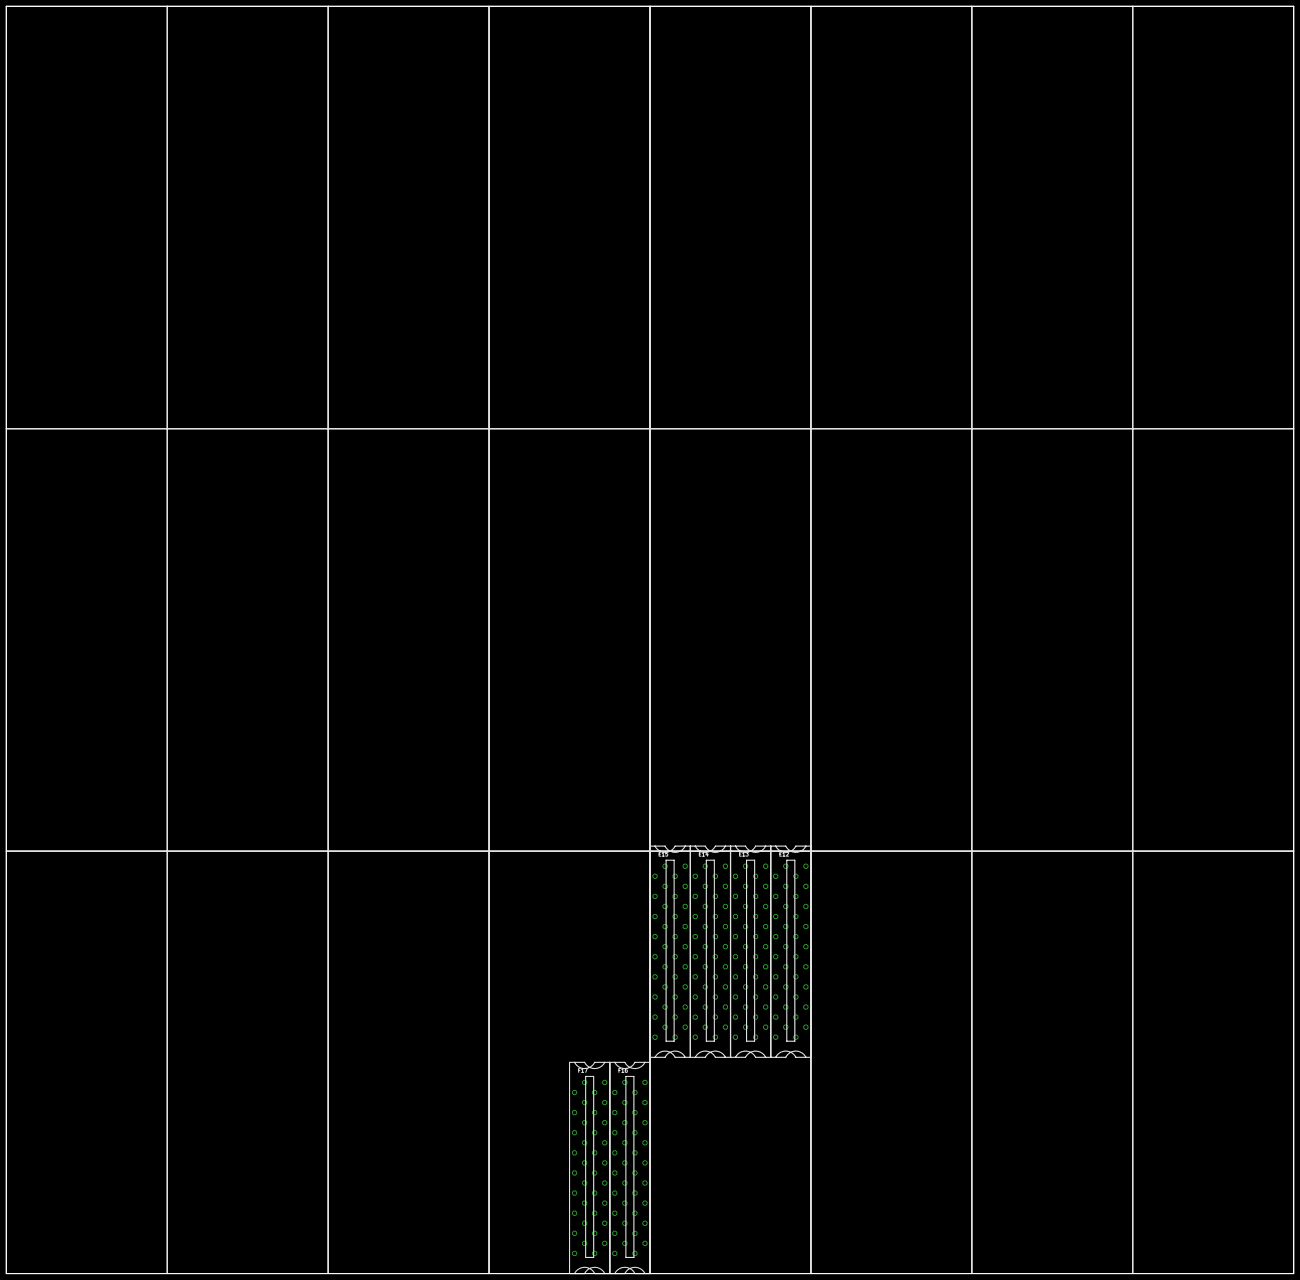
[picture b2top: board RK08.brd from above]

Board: 2 copper layers, 406.4 x 400.1 mm, 30 parts (0 on the bottom side), 2 nets, no tracks yet.

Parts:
E12, E13, E14: M119; H807
E15: M405; H807
F16: M119; H807
F17: M111; H807
U$1, U$2, U$3, U$4, U$5, U$6, U$7, U$8, U$9, U$10, U$11, U$12, U$13, U$14, U$15, U$16, U$17, U$18, U$19, U$20, U$21, U$22, U$23, U$24: CBLOCK

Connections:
GND: E12.C2, E12.T1, E13.C2, E13.T1, E14.C2, E14.T1, F16.C2, F16.T1, F17.C2, F17.T1
VCC: E12.A2, E13.A2, E14.A2, F16.A2, F17.A2
